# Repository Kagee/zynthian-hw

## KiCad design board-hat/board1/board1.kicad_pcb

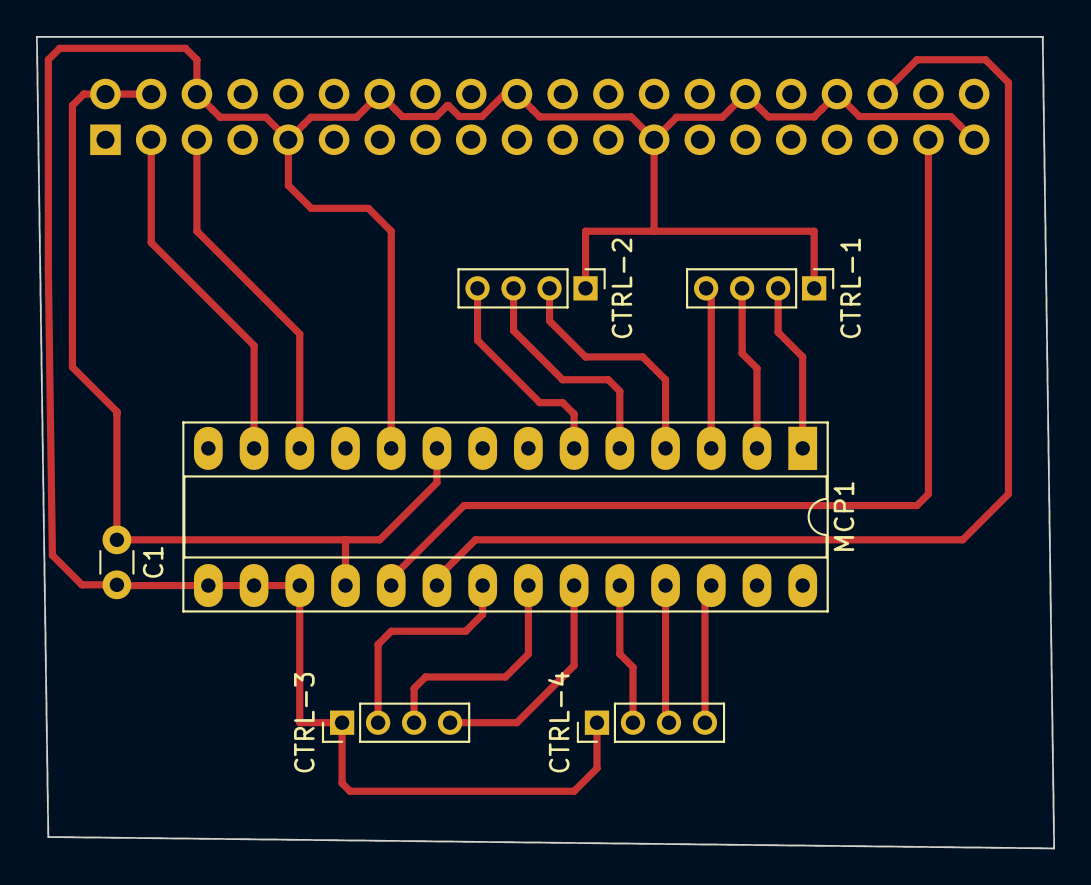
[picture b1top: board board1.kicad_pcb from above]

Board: 2 copper layers, 56.5 x 45.1 mm, 7 parts (1 on the bottom side), 19 nets.

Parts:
C1: 100n; C_Disc_D3.0mm_W1.6mm_P2.50mm
CTRL-1: CTRL3; PinHeader_1x04_P2.00mm_Vertical
CTRL-2: CTRL4; PinHeader_1x04_P2.00mm_Vertical
CTRL-3: CTRL1; PinHeader_1x04_P2.00mm_Vertical
CTRL-4: CTRL2; PinHeader_1x04_P2.00mm_Vertical
MCP1: MCP23017; DIP-28_W7.62mm_Socket_LongPads
P1: Conn_02x20_Odd_Even; PinSocket_2x20_P2.54mm_Vertical

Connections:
+3V3: P1.1, P1.17
+5V: C1.1, MCP1.9, MCP1.18, P1.2, P1.4
/GPIO2(SDA1): MCP1.13, P1.3
/GPIO3(SCL1): MCP1.12, P1.5
/GPIO16: MCP1.20, P1.36
/GPIO26: MCP1.19, P1.37
GND: C1.2, CTRL-1.1, CTRL-2.1, CTRL-3.1, CTRL-4.1, MCP1.10, MCP1.15, MCP1.16, MCP1.17, P1.6, P1.9, P1.14, P1.20, P1.25, P1.30, P1.34, P1.39
unnamed: CTRL-1.2, MCP1.1
unnamed: CTRL-1.3, MCP1.2
unnamed: CTRL-1.4, MCP1.3
unnamed: CTRL-2.2, MCP1.4
unnamed: CTRL-2.3, MCP1.5
unnamed: CTRL-2.4, MCP1.6
unnamed: CTRL-3.2, MCP1.21
unnamed: CTRL-3.3, MCP1.22
unnamed: CTRL-3.4, MCP1.23
unnamed: CTRL-4.2, MCP1.24
unnamed: CTRL-4.3, MCP1.25
unnamed: CTRL-4.4, MCP1.26

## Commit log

2019-10-27 Random playing
